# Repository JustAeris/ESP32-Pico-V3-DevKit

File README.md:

# ESP32 Pico V3 DevKit 🚀

## Overview 📖
This project features a custom PCB designed for the ESP32 Pico V3, including numerous features and allowing for easy developement. 

## Features ✨
- ✅ **USB-programmable ESP32 Pico V3**
- ✅ **Integrated wireless connectivity**
- ✅ **Full access to all pins and a RGB LED**

## Components 🔧
Here’s a list of the major components used:
- 🔌 **ESP32 Pico V3**
- 🔋 **ANT3216LL00R2400A** Chip antenna
- ⚡ **CP2102N** USB to UART IC

## Hardware 🛠️
The hardware includes:
- 📜 [Schematic diagram link](/hardware/ESP32-PICO-V3-DevKit-Schematic.pdf)
- 🖥️ [PCB design link](https://kicanvas.org/?github=https%3A%2F%2Fgithub.com%2FJustAeris%2FESP32-Pico-V3-DevKit%2Ftree%2Fmain%2Fhardware)

## Software 💻
The ESP32 Pico V3 can be programmed either in C or C++ using the Arduino or ESP-IDF framework. It only supports programming via USB as no ESP-PROG nor JTAG interface has been integrated.

## How to Use 🔍
After assembly, it's simply plug and play! (Although you might need the [CP2102N drivers](https://www.silabs.com/developers/usb-to-uart-bridge-vcp-drivers?tab=downloads) if you want to change the USB-UART chip settings.)

## Board Pictures 📸
Here are some pictures of the bare board:

And some pictures of the assembled board:

<details>
   <summary>See more!</summary>
   <br/>

</details>
Feel free to explore the design details and assembly process.

## Known Issues 🐞
There are no known issues for now.
If you encounter any issues, feel free to report them by opening a new issue in the repository.

## License ⚖️
This project is licensed under the GPL-3.0 license - see the LICENSE file for details.

## Contributions 🤝
Feel free to submit issues or pull requests if you find bugs or have suggestions for improvements.

## Contact 📧
For any inquiries, you can reach out to me at [aeris.github@gmail.com](mailto:aeris.github@gmail.com).

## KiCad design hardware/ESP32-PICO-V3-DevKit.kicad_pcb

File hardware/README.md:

# Hardware Overview 🛠️

This folder contains the hardware files for the **ESP32Pico V3 DevKit**. Here you'll find all the necessary designs and documents related to the hardware components of the project.

## Contents 📁
- **PCB Designs**: Schematics and layout files created using KiCad.
- **3D Models**: Any 3D models of the components or the assembled board.
- **Bill of Materials (BOM)**: A list of all components used in the project.

## Files Description 📄
- **[ESP32-PICO-V3-DevKit.kicad_pcb]**: The main PCB layout file.
- **[ESP32-PICO-V3-DevKit.kicad_sch]**: The schematic diagram for the circuit.
- **[ESP32-PICO-V3-DevKit-BOM.csv]**: Bill of materials listing all components.
PDF files for the schematic and gerber layers are also included.

## Getting Started ⚙️
1. Open the PCB design in KiCad to view or modify the layout.
2. Use the schematic to understand the circuit connections.
3. Refer to the BOM for component sourcing.

## License ⚖️
This hardware design is licensed under the **GPL-3.0 license**. See the [LICENSE](../LICENSE) file for details.

## Contributing 🤝
If you have suggestions or improvements for the hardware design, feel free to create a pull request or open an issue.

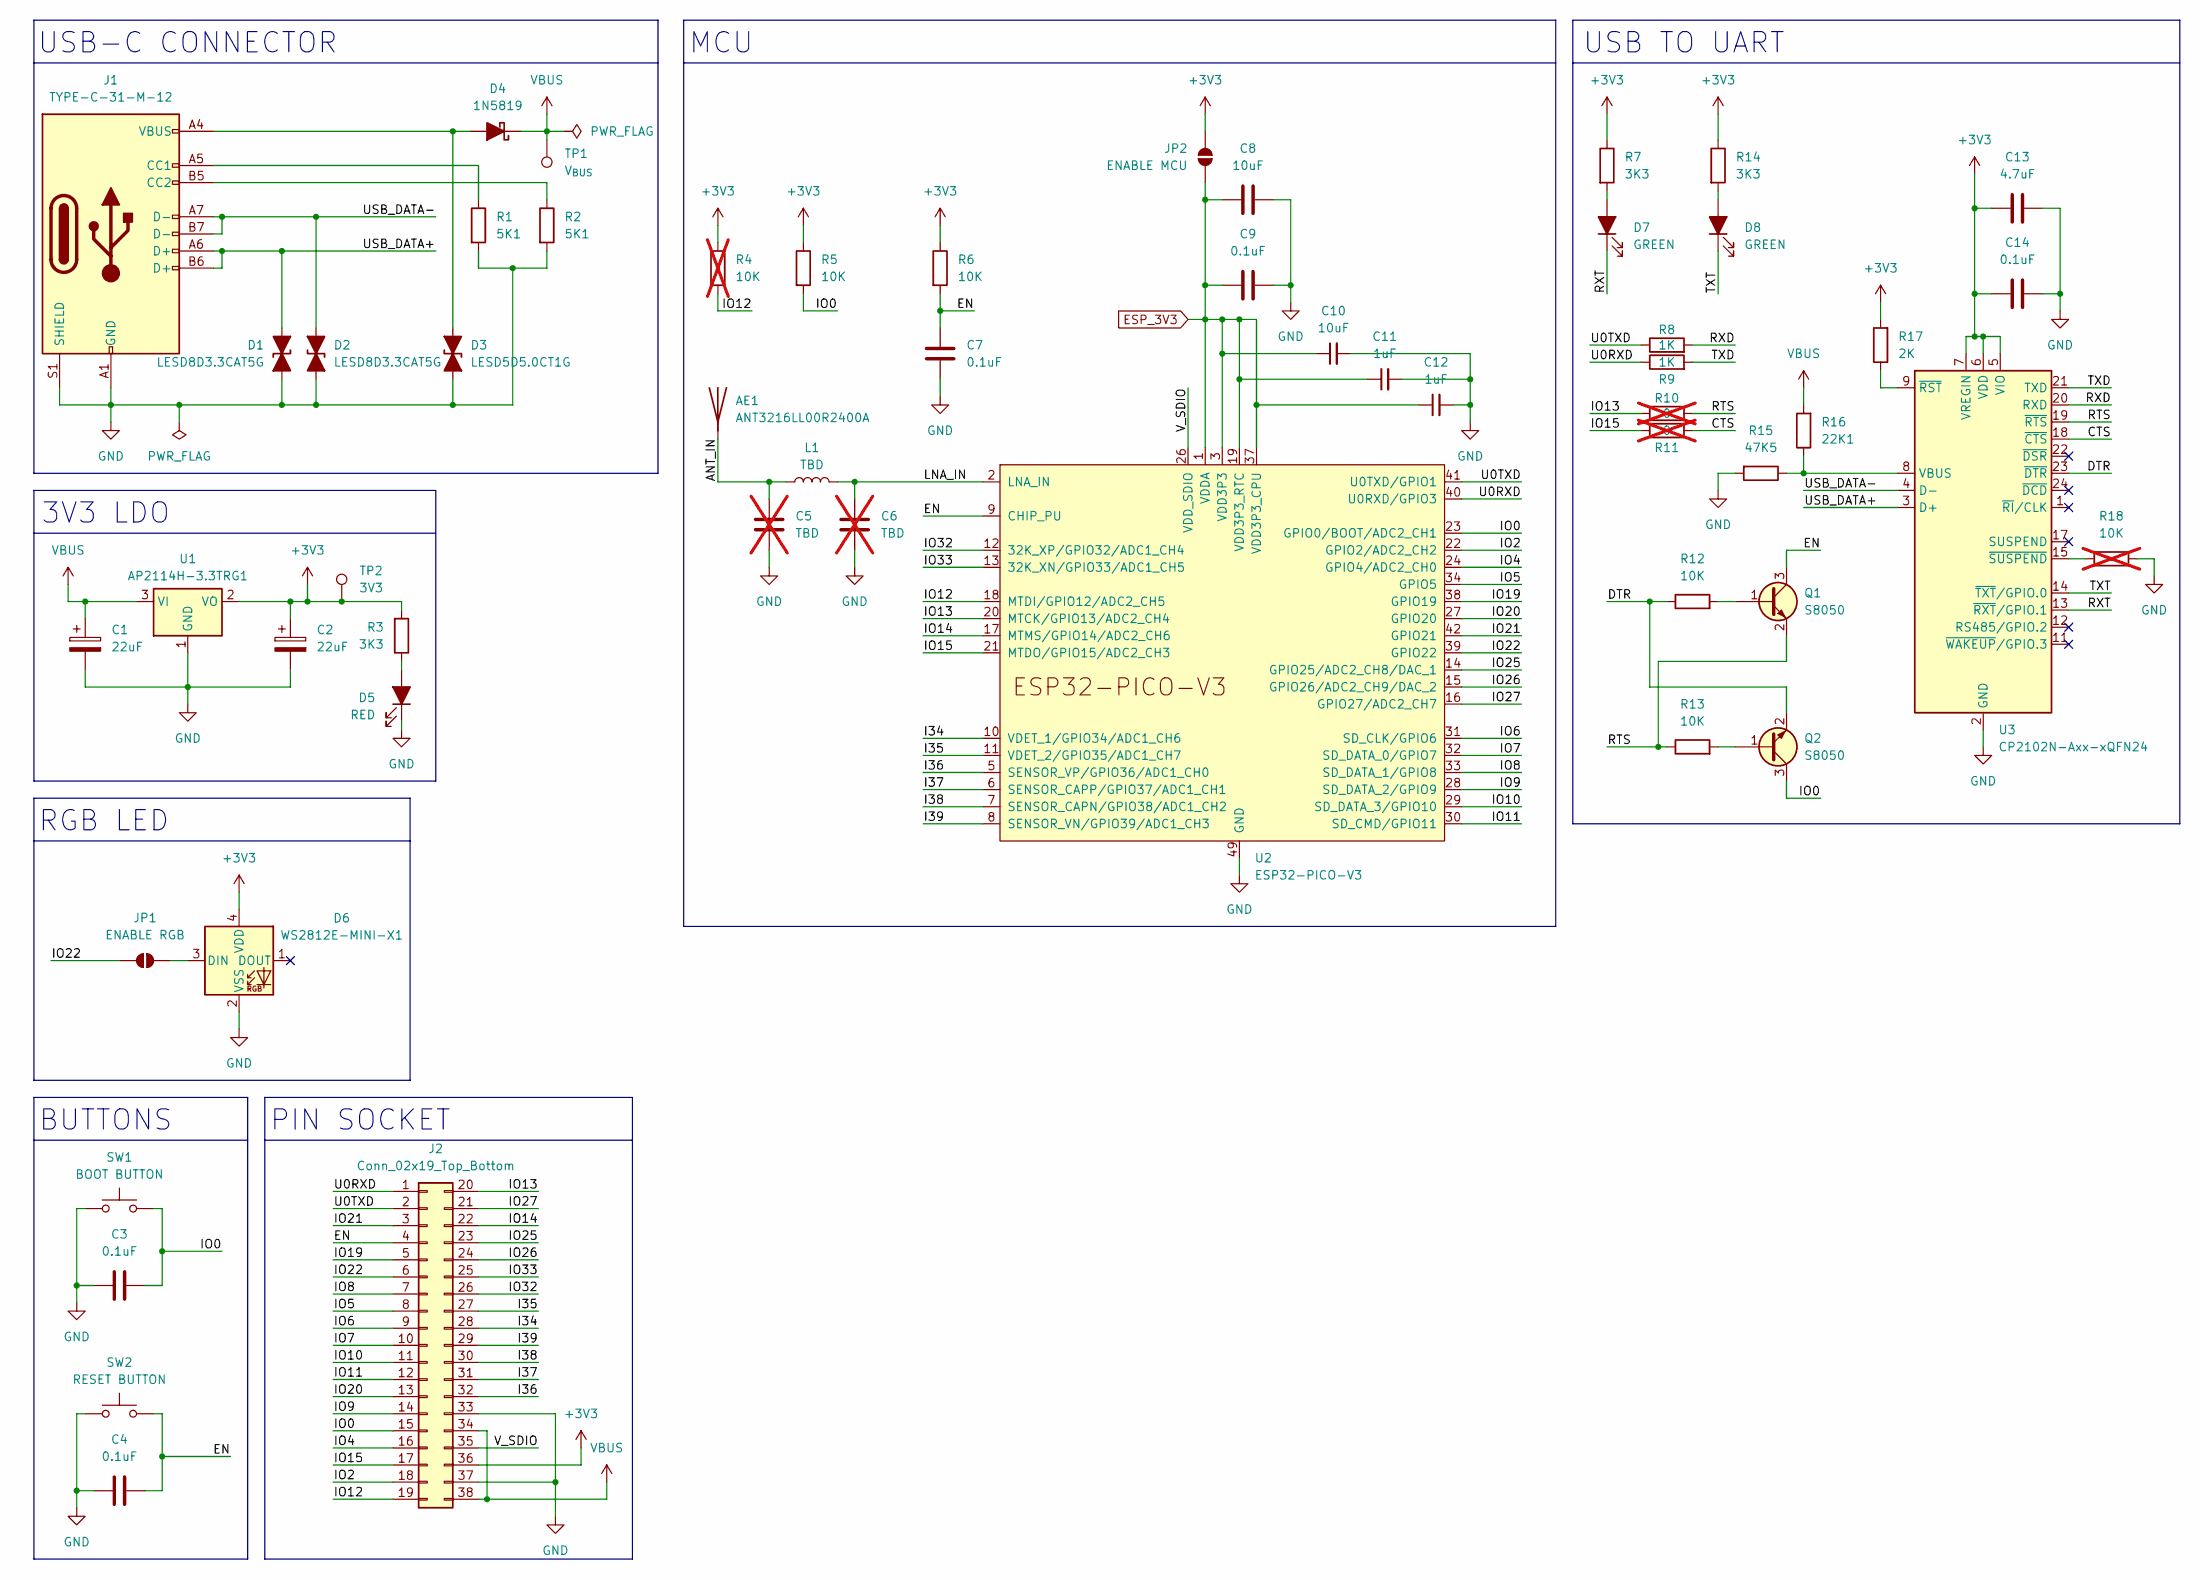
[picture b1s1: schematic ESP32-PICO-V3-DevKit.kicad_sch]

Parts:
AE1: ANT3216LL00R2400A
C1, C2: 22uF; C_0805_2012Metric
C3, C4, C7, C9, C14: 0.1uF; C_0402_1005Metric
C5, C6: TBD; C_0402_1005Metric; not fitted
C8, C10: 10uF; C_0402_1005Metric
C11, C12: 1uF; C_0402_1005Metric
C13: 4.7uF; C_0402_1005Metric
D1, D2: LESD8D3.3CAT5G; D_SOD-882_DFN1006-2_TVS
D3: LESD5D5.0CT1G; D_SOD-523_TVS
D4: 1N5819; D_SOD-123
D5: RED; LED_0805_2012Metric
D6: WS2812E-MINI-X1; LED_SK6812MINI_PLCC4_3.5x3.5mm_P1.75mm
D7, D8: GREEN; LED_0805_2012Metric
J1: TYPE-C-31-M-12; USB_C_Receptacle_HRO_TYPE-C-31-M-12
J2: Conn_02x19_Top_Bottom; PinSocket_2x19_P2.54mm_Vertical_SMD
JP1: ENABLE RGB; SolderJumper-2_P1.3mm_Open_TrianglePad1.0x1.5mm
JP2: ENABLE MCU; SolderJumper-2_P1.3mm_Open_RoundedPad1.0x1.5mm
L1: TBD; L_0402_1005Metric
Q1, Q2: S8050; SOT-23
R1, R2: 5K1; R_0402_1005Metric
R3, R7, R14: 3K3; R_0402_1005Metric
R4, R18: 10K; R_0402_1005Metric; not fitted
R5, R6, R12, R13: 10K; R_0402_1005Metric
R8, R9: 1K; R_0402_1005Metric
R10, R11: 0; R_0402_1005Metric; not fitted
R15: 47K5; R_0402_1005Metric
R16: 22K1; R_0402_1005Metric
R17: 2K; R_0402_1005Metric
SW1: BOOT BUTTON; SW_Push_1P1T_XKB_TS-1187A
SW2: RESET BUTTON; SW_Push_1P1T_XKB_TS-1187A
TP1: V_{BUS}; TestPoint_Pad_D1.0mm
TP2: 3V3; TestPoint_Pad_D1.0mm
U1: AP2114H-3.3TRG1; SOT-223-3_TabPin2
U2: ESP32-PICO-V3; QFN-48-1EP_7x7mm_P0.5mm_EP5.1x5.1mm
U3: CP2102N-Axx-xQFN24; QFN-24-1EP_4x4mm_P0.5mm_EP2.6x2.6mm

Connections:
+3V3: C2.1, C13.2, C14.2, D6.4 (VDD), J2.36, JP2.2 (B), R3.2, R4.1, R5.1, R6.1, R7.1, R14.1, R17.2, TP2.1, U1.2 (VO), U3.5 (VIO), U3.6 (VDD), U3.7 (VREGIN)
/ANT_IN: AE1.1 (A), C5.1, L1.1
/CTS: R11.2, U3.18 (~CTS)
/DTR: Q2.2 (E), R12.1, U3.23 (~DTR)
/EN: C4.2, C7.1, J2.4, Q1.3 (C), R6.2, SW2.2, U2.9 (CHIP_PU)
/I34: J2.28, U2.10 (VDET_1/GPIO34/ADC1_CH6)
/I35: J2.27, U2.11 (VDET_2/GPIO35/ADC1_CH7)
/I36: J2.32, U2.5 (SENSOR_VP/GPIO36/ADC1_CH0)
/I37: J2.31, U2.6 (SENSOR_CAPP/GPIO37/ADC1_CH1)
/I38: J2.30, U2.7 (SENSOR_CAPN/GPIO38/ADC1_CH2)
/I39: J2.29, U2.8 (SENSOR_VN/GPIO39/ADC1_CH3)
/IO0: C3.2, J2.15, Q2.3 (C), R5.2, SW1.2, U2.23 (GPIO0/BOOT/ADC2_CH1)
/IO2: J2.18, U2.22 (GPIO2/ADC2_CH2)
/IO4: J2.16, U2.24 (GPIO4/ADC2_CH0)
/IO5: J2.8, U2.34 (GPIO5)
/IO6: J2.9, U2.31 (SD_CLK/GPIO6)
/IO7: J2.10, U2.32 (SD_DATA_0/GPIO7)
/IO8: J2.7, U2.33 (SD_DATA_1/GPIO8)
/IO9: J2.14, U2.28 (SD_DATA_2/GPIO9)
/IO10: J2.11, U2.29 (SD_DATA_3/GPIO10)
/IO11: J2.12, U2.30 (SD_CMD/GPIO11)
/IO12: J2.19, R4.2, U2.18 (MTDI/GPIO12/ADC2_CH5)
/IO13: J2.20, R10.1, U2.20 (MTCK/GPIO13/ADC2_CH4)
/IO14: J2.22, U2.17 (MTMS/GPIO14/ADC2_CH6)
/IO15: J2.17, R11.1, U2.21 (MTDO/GPIO15/ADC2_CH3)
/IO19: J2.5, U2.38 (GPIO19)
/IO20: J2.13, U2.27 (GPIO20)
/IO21: J2.3, U2.42 (GPIO21)
/IO22: J2.6, JP1.1 (A), U2.39 (GPIO22)
/IO25: J2.23, U2.14 (GPIO25/ADC2_CH8/DAC_1)
/IO26: J2.24, U2.15 (GPIO26/ADC2_CH9/DAC_2)
/IO27: J2.21, U2.16 (GPIO27/ADC2_CH7)
/IO32: J2.26, U2.12 (32K_XP/GPIO32/ADC1_CH4)
/IO33: J2.25, U2.13 (32K_XN/GPIO33/ADC1_CH5)
/LNA_IN: C6.1, L1.2, U2.2 (LNA_IN)
/RTS: Q1.2 (E), R10.2, R13.1, U3.19 (~RTS)
/RXD: R8.2, U3.20 (RXD)
/RXT: D7.1 (K), U3.13 (~RXT/GPIO.1)
/TXD: R9.2, U3.21 (TXD)
/TXT: D8.1 (K), U3.14 (~TXT/GPIO.0)
/U0RXD: J2.1, R9.1, U2.40 (U0RXD/GPIO3)
/U0TXD: J2.2, R8.1, U2.41 (U0TXD/GPIO1)
/USB_DATA+: D1.2 (A2), J1.A6 (D+), J1.B6 (D+), U3.3 (D+)
/USB_DATA-: D2.2 (A2), J1.A7 (D-), J1.B7 (D-), U3.4 (D-)
/V_SDIO: J2.35, U2.26 (VDD_SDIO)
ESP_3V3: C8.2, C9.2, C10.1, C11.1, C12.1, JP2.1 (A), U2.1 (VDDA), U2.3 (VDD3P3), U2.4 (VDD3P3), U2.19 (VDD3P3_RTC), U2.37 (VDD3P3_CPU), U2.43 (VDDA), U2.46 (VDDA)
GND: C1.2, C2.2, C3.1, C4.1, C5.2, C6.2, C7.2, C8.1, C9.1, C10.2, C11.2, C12.2, C13.1, C14.1, D1.1 (A1), D2.1 (A1), D3.1 (A1), D5.1 (K), D6.2 (VSS), J1.A1 (GND), J1.A12 (GND), J1.B1 (GND), J1.B12 (GND), J1.S1 (SHIELD), J2.33, J2.37, R1.2, R2.2, R15.2, R18.2, SW1.1, SW2.1, U1.1 (GND), U2.49 (GND), U3.2 (GND), U3.25 (GND)
unnamed: D3.2 (A2), D4.2 (A), J1.A4 (VBUS), J1.A9 (VBUS), J1.B4 (VBUS), J1.B9 (VBUS)
unnamed: D5.2 (A), R3.1
unnamed: D6.3 (DIN), JP1.2 (B)
unnamed: D7.2 (A), R7.2
unnamed: D8.2 (A), R14.2
unnamed: J1.A5 (CC1), R1.1
unnamed: J1.B5 (CC2), R2.1
unnamed: Q1.1 (B), R12.2
unnamed: Q2.1 (B), R13.2
unnamed: R15.1, R16.1, U3.8 (VBUS)
unnamed: R17.1, U3.9 (~RST)
unnamed: R18.1, U3.15 (~SUSPEND)
VBUS: C1.1, D4.1 (K), J2.34, J2.38, R16.2, TP1.1, U1.3 (VI)

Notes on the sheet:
RGB LED
USB TO UART
BUTTONS
3V3 LDO
MCU
USB-C CONNECTOR
PIN SOCKET

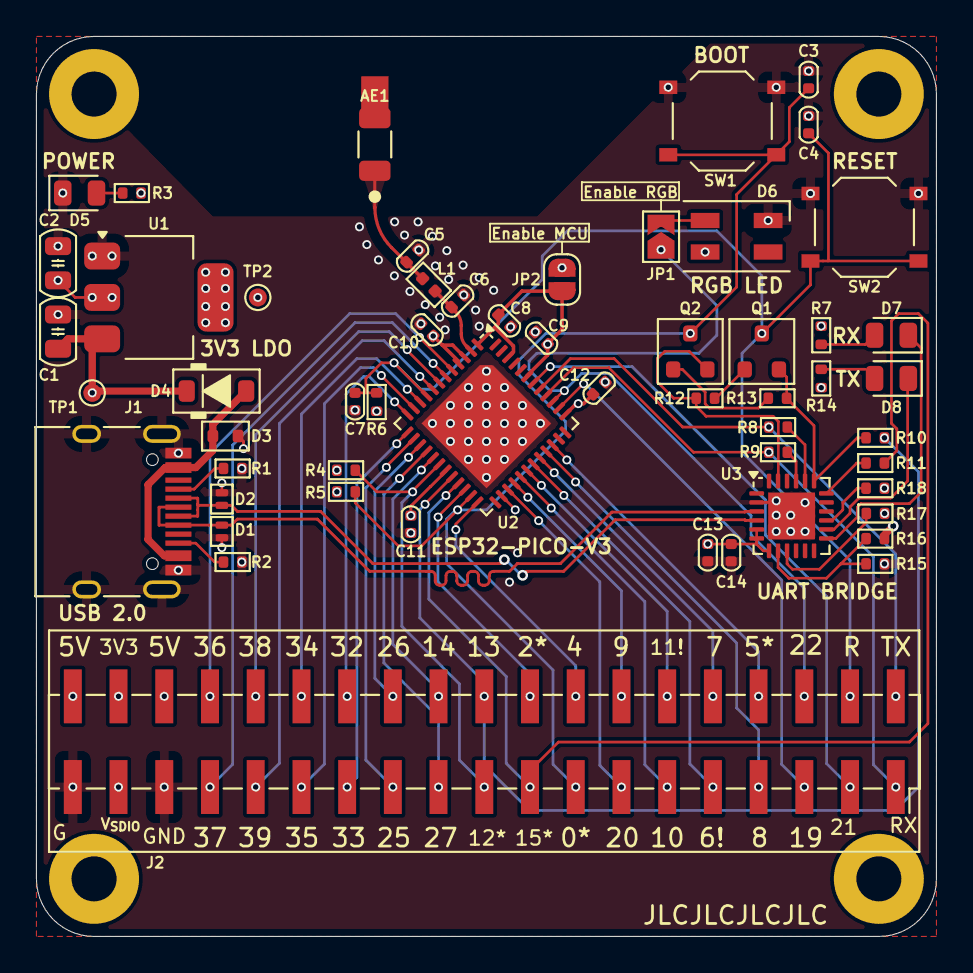
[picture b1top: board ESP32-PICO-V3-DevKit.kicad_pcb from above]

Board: 6 copper layers, 50.0 x 50.0 mm, 55 parts (0 on the bottom side), 60 nets.

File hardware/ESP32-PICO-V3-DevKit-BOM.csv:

"Reference","Value","Datasheet","Footprint","Qty","DNP"
"AE1","ANT3216LL00R2400A","~","Personal-Library:ANT3216LL00R2400A","1",""
"C1,C2","22uF","~","Capacitor_SMD_Handsoldering_AKL:C_0805_2012Metric","2",""
"C3,C4,C7,C9,C14","0.1uF","~","Capacitor_SMD_US_Handsoldering_AKL:C_0402_1005Metric","5",""
"C5,C6","TBD","~","Capacitor_SMD_US_Handsoldering_AKL:C_0402_1005Metric","2","DNP"
"C8,C10","10uF","~","Capacitor_SMD_US_Handsoldering_AKL:C_0402_1005Metric","2",""
"C11,C12","1uF","~","Capacitor_SMD_US_Handsoldering_AKL:C_0402_1005Metric","2",""
"C13","4.7uF","~","Capacitor_SMD_US_Handsoldering_AKL:C_0402_1005Metric","1",""
"D1,D2","LESD8D3.3CAT5G","~","Diode_SMD_Handsoldering_AKL:D_SOD-882_DFN1006-2_TVS","2",""
"D3","LESD5D5.0CT1G","~","Diode_SMD_AKL:D_SOD-523_TVS","1",""
"D4","1N5819","https://www.tme.eu/Document/1dcb17797cd83f32e896ece3030f14cc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","Diode_SMD_Handsoldering_AKL:D_SOD-123","1",""
"D5","RED","~","LED_SMD:LED_0805_2012Metric","1",""
"D6","WS2812E-MINI-X1","https://cdn-shop.adafruit.com/product-files/2686/SK6812MINI_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","LED_SMD:LED_SK6812MINI_PLCC4_3.5x3.5mm_P1.75mm","1",""
"D7,D8","GREEN","~","LED_SMD:LED_0805_2012Metric","2",""
"J1","TYPE-C-31-M-12","https://www.usb.org/sites/default/files/documents/usb_type-c.zip","Connector_USB:USB_C_Receptacle_HRO_TYPE-C-31-M-12","1",""
"J2","Conn_02x19_Top_Bottom","~","Connector_PinSocket_2.54mm:PinSocket_2x19_P2.54mm_Vertical_SMD","1",""
"L1","TBD","~","Inductor_SMD_Handsoldering_AKL:L_0402_1005Metric","1",""
"Q1,Q2","S8050","https://www.tme.eu/Document/724c1368d1e41c0842e24711fa206132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","Package_TO_SOT_SMD_AKL:SOT-23","2",""
"R1,R2","5K1","~","Resistor_SMD_AKL:R_0402_1005Metric","2",""
"R3,R7,R14","3K3","~","Resistor_SMD_AKL:R_0402_1005Metric","3",""
"R4,R18","10K","~","Resistor_SMD_AKL:R_0402_1005Metric","2","DNP"
"R5,R6,R12,R13","10K","~","Resistor_SMD_AKL:R_0402_1005Metric","4",""
"R8,R9","1K","~","Resistor_SMD_AKL:R_0402_1005Metric","2",""
"R10,R11","0","~","Resistor_SMD_AKL:R_0402_1005Metric","2","DNP"
"R15","47K5","~","Resistor_SMD_AKL:R_0402_1005Metric","1",""
"R16","22K1","~","Resistor_SMD_AKL:R_0402_1005Metric","1",""
"R17","2K","~","Resistor_SMD_AKL:R_0402_1005Metric","1",""
"SW1","BOOT BUTTON","~","Button_Switch_SMD:SW_Push_1P1T_XKB_TS-1187A","1",""
"SW2","RESET BUTTON","~","Button_Switch_SMD:SW_Push_1P1T_XKB_TS-1187A","1",""
"TP1","V_{BUS}","~","TestPoint:TestPoint_Pad_D1.0mm","1",""
"TP2","3V3","~","TestPoint:TestPoint_Pad_D1.0mm","1",""
"U1","AP2114H-3.3TRG1","https://www.lcsc.com/datasheet/lcsc_datasheet_2304140030_Dio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","Package_TO_SOT_SMD:SOT-223-3_TabPin2","1",""
"U2","ESP32-PICO-V3","https://www.espressif.com/sites/default/files/documentation/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","Package_DFN_QFN:QFN-48-1EP_7x7mm_P0.5mm_EP5.1x5.1mm","1",""
"U3","CP2102N-Axx-xQFN24","https://www.silabs.com/documents/public/data-sheets/cp2102n-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","Package_DFN_QFN:QFN-24-1EP_4x4mm_P0.5mm_EP2.6x2.6mm","1",""
